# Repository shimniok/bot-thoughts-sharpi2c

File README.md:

A2D converts analog for you and presents it digitally through I2C, SPI or Serial. 
The onboard ATtiny performs oversampling and filtering to reduce noise. Flexible and hackable, 
you can program the device with AVRISP and make use of any of the exposed GPIO pins.

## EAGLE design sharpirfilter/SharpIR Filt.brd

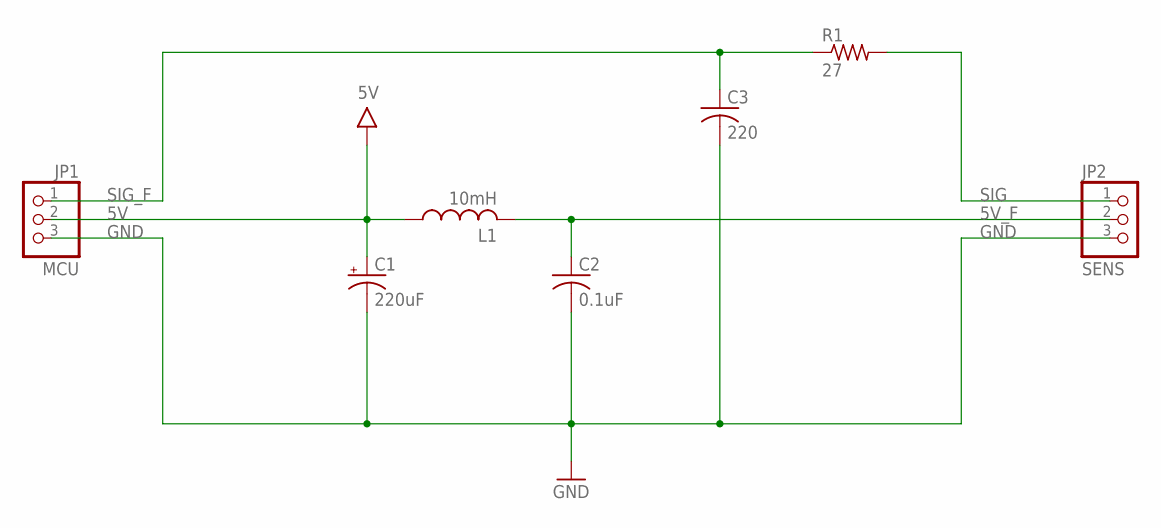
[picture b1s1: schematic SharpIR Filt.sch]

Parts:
C1: 220uF; PANASONIC_C
C2: 0.1uF; C0603
C3: 220; C0603
JP1: MCU; 1X03M
JP2: SENS; 1X03M
L1: 10mH; L5650M
R1: 27; R0603

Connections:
5V: C1.+, JP1.2, L1.1
5V_F: C2.1, JP2.2, L1.2
GND: C1.-, C2.2, C3.2, JP1.3, JP2.3
SIG: JP2.1, R1.2
SIG_F: C3.1, JP1.1, R1.1

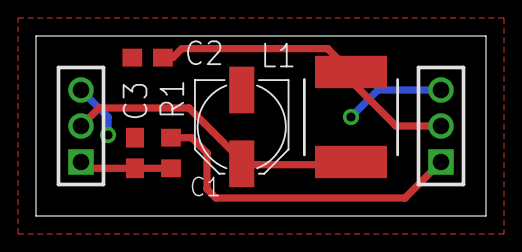
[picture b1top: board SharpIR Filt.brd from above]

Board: 2 copper layers, 25.0 x 10.0 mm, 7 parts (0 on the bottom side), 5 nets.

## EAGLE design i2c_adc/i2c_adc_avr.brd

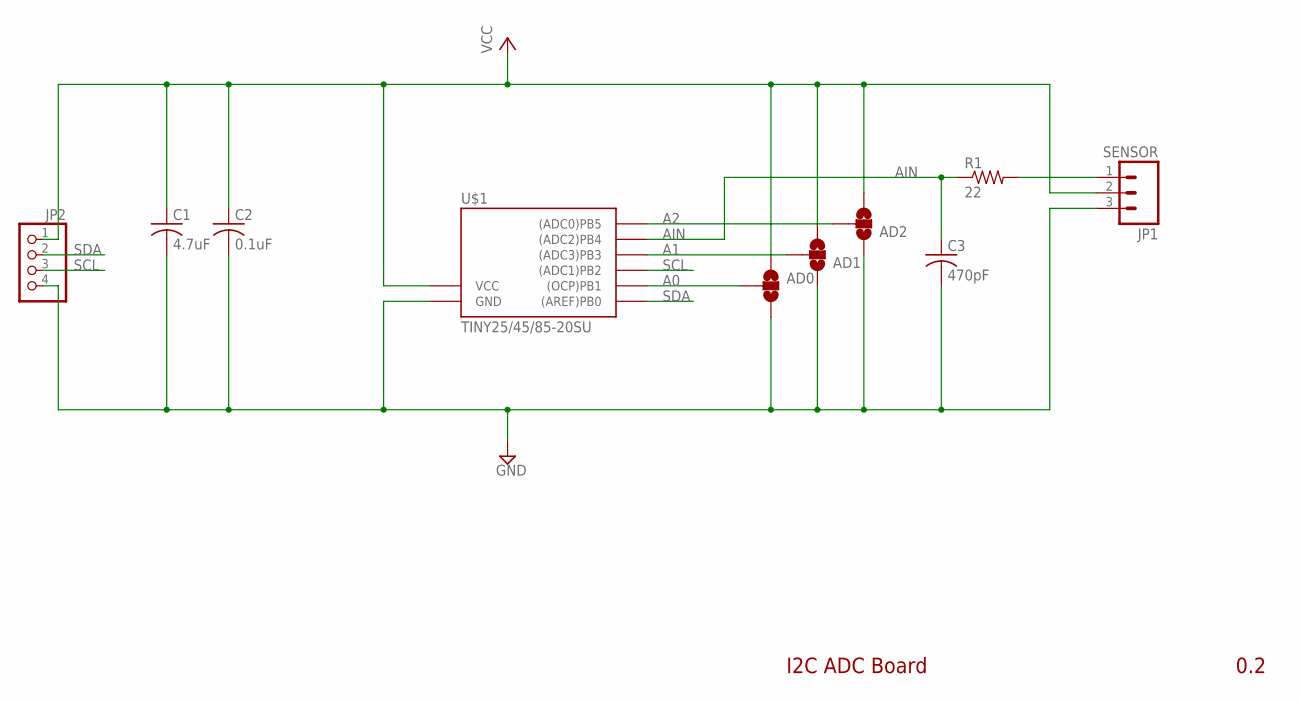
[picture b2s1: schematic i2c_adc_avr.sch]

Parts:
AD0, AD1, AD2: SOLDERJUMPER_2WAYS; SJ_3
C1: 4.7uF; C0603
C2: 0.1uF; C0603
C3: 470pF; C0603
JP1: SENSOR; 1X03
JP2: PINHD-1X04_2.54-S; 1X04-S
R1: 22; R0603
U$1: TINY25/45/85-20SU; SOIC8

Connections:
A0: AD0.2, U$1.6 ((OCP)PB1)
A1: AD1.2, U$1.2 ((ADC3)PB3)
A2: AD2.2, U$1.1 ((ADC0)PB5)
AIN: C3.1, R1.1, U$1.3 ((ADC2)PB4)
GND: AD0.3, AD1.1, AD2.1, C1.2, C2.2, C3.2, JP1.3, JP2.4, U$1.4 (GND)
unnamed: JP1.1, R1.2
SCL: JP2.3, U$1.7 ((ADC1)PB2)
SDA: JP2.2, U$1.5 ((AREF)PB0)
VCC: AD0.1, AD1.3, AD2.3, C1.1, C2.1, JP1.2, JP2.1, U$1.8 (VCC)

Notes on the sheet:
I2C ADC Board
0.2

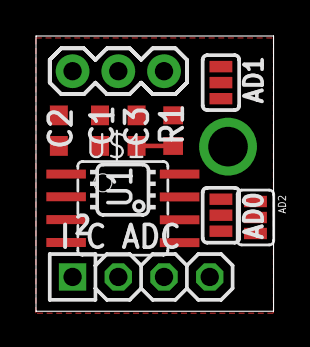
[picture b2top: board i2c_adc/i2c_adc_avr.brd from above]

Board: 2 copper layers, 13.2 x 15.3 mm, 10 parts (0 on the bottom side), 9 nets.

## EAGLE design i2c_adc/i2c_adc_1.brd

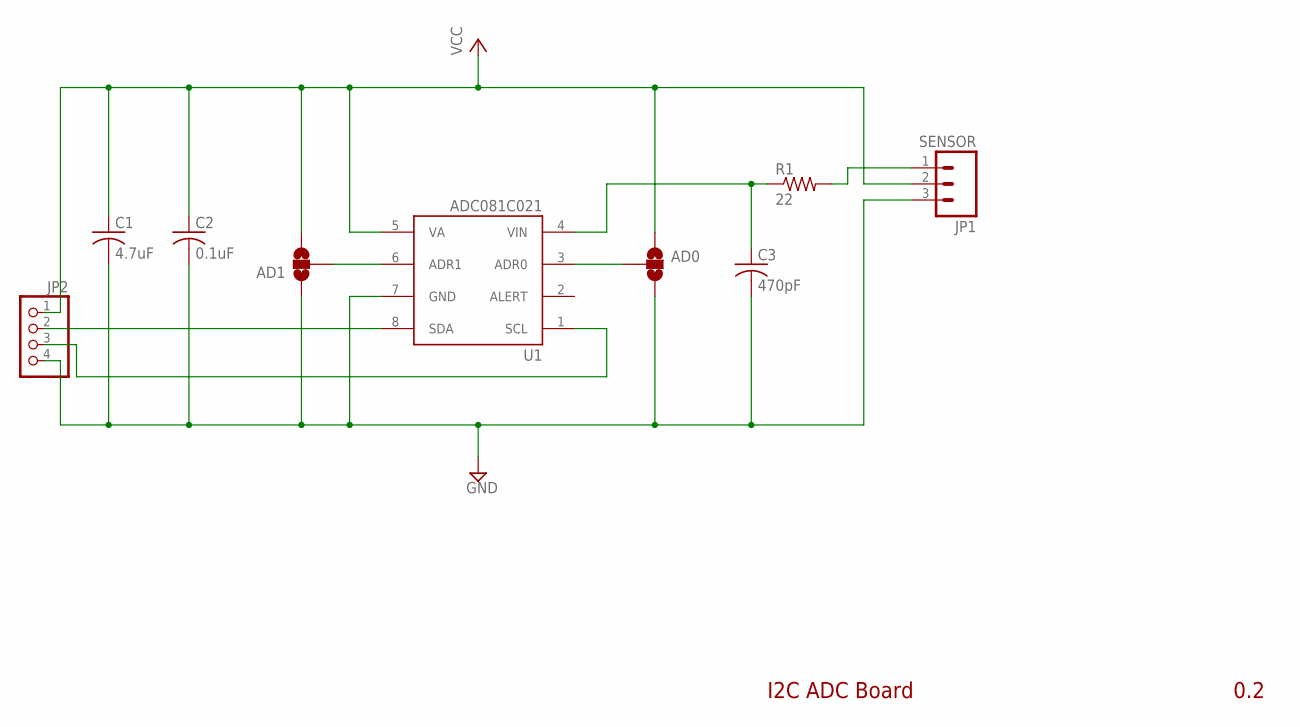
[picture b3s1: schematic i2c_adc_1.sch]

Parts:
AD0, AD1: SOLDERJUMPER_2WAYS; SJ_3
C1: 4.7uF; C0603
C2: 0.1uF; C0603
C3: 470pF; C0603
JP1: SENSOR; 1X03
JP2: PINHD-1X04_2.54-S; 1X04-S
R1: 22; R0603
U1: ADC081C021; MSOP8_0.65

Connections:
GND: AD0.3, AD1.1, C1.2, C2.2, C3.2, JP1.3, JP2.4, U1.7 (GND)
unnamed: JP1.1, R1.2
unnamed: AD1.2, U1.6 (ADR1)
unnamed: AD0.2, U1.3 (ADR0)
unnamed: C3.1, R1.1, U1.4 (VIN)
SCL: JP2.3, U1.1 (SCL)
SDA: JP2.2, U1.8 (SDA)
VCC: AD0.1, AD1.3, C1.1, C2.1, JP1.2, JP2.1, U1.5 (VA)

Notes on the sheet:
I2C ADC Board
0.2

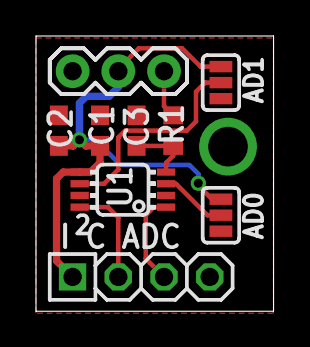
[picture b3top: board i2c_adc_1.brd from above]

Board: 2 copper layers, 13.2 x 15.3 mm, 9 parts (0 on the bottom side), 8 nets.

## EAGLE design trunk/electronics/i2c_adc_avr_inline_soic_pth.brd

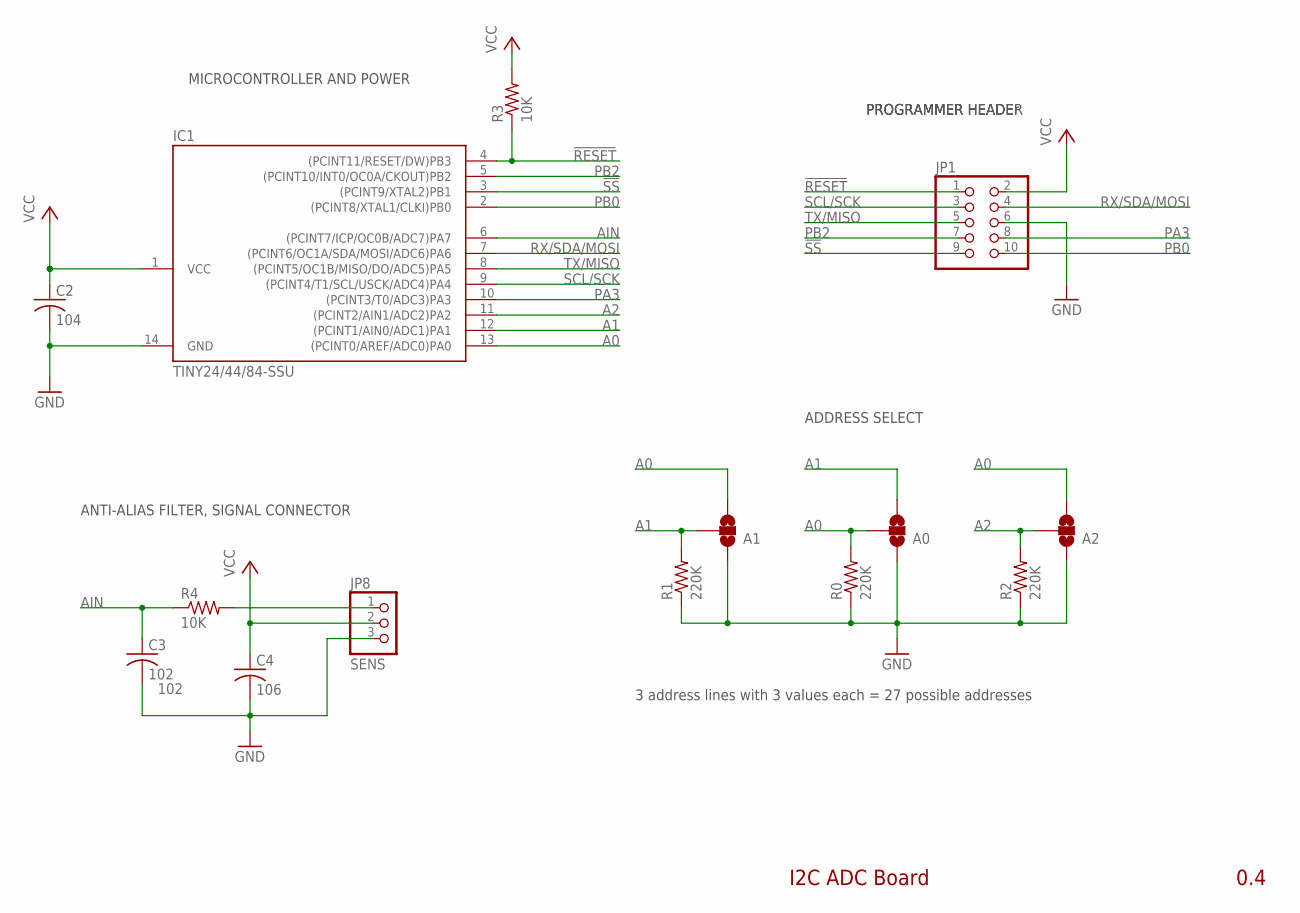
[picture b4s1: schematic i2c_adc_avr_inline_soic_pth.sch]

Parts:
A0, A1, A2: SJ_3
C2: 104; C0603; PARTNO C1608X7R1E104K080AA
C3: 102; C0603; PARTNO CL10B102KB8SFNC
C4: 106; C0603; PARTNO CL10A106MP8NNNC
IC1: TINY24/44/84-SSU; SOIC14
JP1: PINHD-2X05_2.54-90°; 2X05/90
JP8: SENS; 1X03-S
R0, R1, R2: 220K; R0603; PARTNO RC1608J224CS
R3, R4: 10K; R0603; PARTNO 1622829-1

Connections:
!RESET: IC1.4 ((PCINT11/RESET/DW)PB3), JP1.1, R3.1
!SS: IC1.3 ((PCINT9/XTAL2)PB1), JP1.9
A0: A0.2, A1.3, A2.3, IC1.13 ((PCINT0/AREF/ADC0)PA0), R0.2
A1: A0.3, A1.2, IC1.12 ((PCINT1/AIN0/ADC1)PA1), R1.2
A2: A2.2, IC1.11 ((PCINT2/AIN1/ADC2)PA2), R2.2
AIN: C3.1, IC1.6 ((PCINT7/ICP/OC0B/ADC7)PA7), R4.1
GND: A0.1, A1.1, A2.1, C2.2, C3.2, C4.2, IC1.14 (GND), JP1.6, JP8.3, R0.1, R1.1, R2.1
unnamed: JP8.1, R4.2
PA3: IC1.10 ((PCINT3/T0/ADC3)PA3), JP1.8
PB0: IC1.2 ((PCINT8/XTAL1/CLKI)PB0), JP1.10
PB2: IC1.5 ((PCINT10/INT0/OC0A/CKOUT)PB2), JP1.7
RX/SDA/MOSI: IC1.7 ((PCINT6/OC1A/SDA/MOSI/ADC6)PA6), JP1.4
SCL/SCK: IC1.9 ((PCINT4/T1/SCL/USCK/ADC4)PA4), JP1.3
TX/MISO: IC1.8 ((PCINT5/OC1B/MISO/DO/ADC5)PA5), JP1.5
VCC: C2.1, C4.1, IC1.1 (VCC), JP1.2, JP8.2, R3.2

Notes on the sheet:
I2C ADC Board
0.4
ADDRESS SELECT
MICROCONTROLLER AND POWER
ANTI-ALIAS FILTER, SIGNAL CONNECTOR
3 address lines with 3 values each = 27 possible addresses
PROGRAMMER HEADEr
PROGRAMMER HEADER

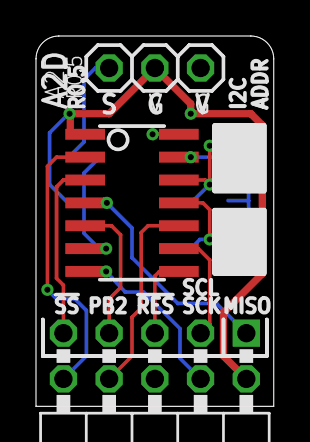
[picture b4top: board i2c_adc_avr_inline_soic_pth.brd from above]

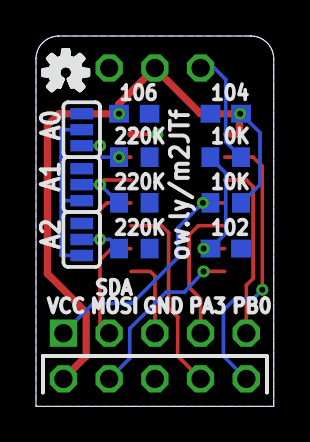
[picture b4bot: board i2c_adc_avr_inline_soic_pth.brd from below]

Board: 2 copper layers, 13.2 x 20.6 mm, 14 parts (11 on the bottom side), 15 nets.

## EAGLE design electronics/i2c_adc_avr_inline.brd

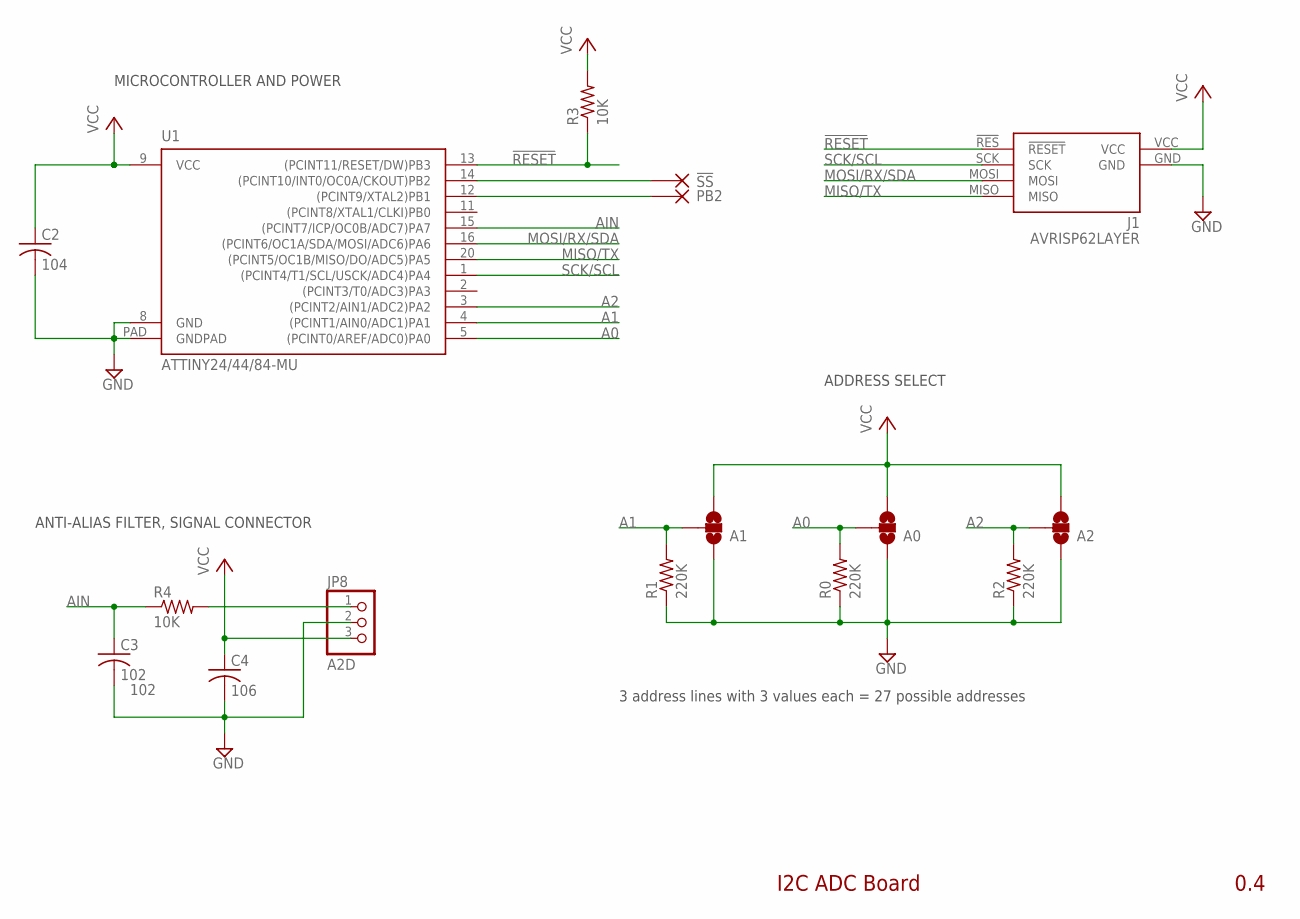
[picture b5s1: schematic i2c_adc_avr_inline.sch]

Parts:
A0, A1, A2: SJ_3
C2: 104; C0603; PARTNO C1608X7R1E104K080AA
C3: 102; C0603; PARTNO CL10B102KB8SFNC
C4: 106; C0603; PARTNO CL10A106MP8NNNC
J1: AVRISP62LAYER; 2X3_2LAYER
JP8: A2D; 1X03-S
R0, R1, R2: 220K; R0603; PARTNO RC1608J224CS
R3, R4: 10K; R0603; PARTNO 1622829-1
U1: ATTINY24/44/84-MU; 20MLF_0.5
X1: !SS; PAD0.07X0.15
X4: PB2; PAD0.07X0.15

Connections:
!RESET: J1.!RES (!RESET), R3.1, U1.13 ((PCINT11/RESET/DW)PB3)
A0: A0.2, R0.2, U1.5 ((PCINT0/AREF/ADC0)PA0)
A1: A1.2, R1.2, U1.4 ((PCINT1/AIN0/ADC1)PA1)
A2: A2.2, R2.2, U1.3 ((PCINT2/AIN1/ADC2)PA2)
AIN: C3.1, R4.1, U1.15 ((PCINT7/ICP/OC0B/ADC7)PA7)
GND: A0.1, A1.1, A2.1, C2.2, C3.2, C4.2, J1.GND, JP8.2, R0.1, R1.1, R2.1, U1.8 (GND), U1.PAD (GNDPAD)
MISO/TX: J1.MISO, U1.20 ((PCINT5/OC1B/MISO/DO/ADC5)PA5)
MOSI/RX/SDA: J1.MOSI, U1.16 ((PCINT6/OC1A/SDA/MOSI/ADC6)PA6)
unnamed: JP8.1, R4.2
unnamed: U1.14 ((PCINT10/INT0/OC0A/CKOUT)PB2), X1.P$1
unnamed: U1.12 ((PCINT9/XTAL2)PB1), X4.P$1
SCK/SCL: J1.SCK, U1.1 ((PCINT4/T1/SCL/USCK/ADC4)PA4)
VCC: A0.3, A1.3, A2.3, C2.1, C4.1, J1.VCC, JP8.3, R3.2, U1.9 (VCC)

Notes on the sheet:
I2C ADC Board
0.4
ADDRESS SELECT
MICROCONTROLLER AND POWER
ANTI-ALIAS FILTER, SIGNAL CONNECTOR
3 address lines with 3 values each = 27 possible addresses

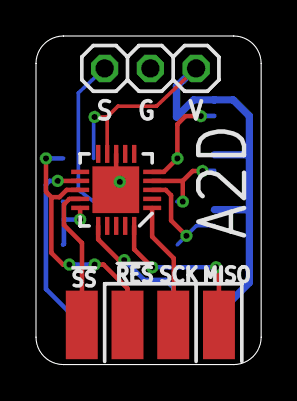
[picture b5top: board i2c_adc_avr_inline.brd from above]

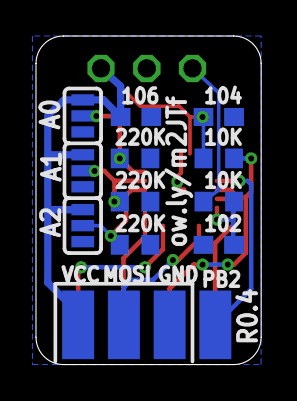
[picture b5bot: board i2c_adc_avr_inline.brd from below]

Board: 2 copper layers, 12.5 x 18.3 mm, 16 parts (12 on the bottom side), 13 nets.

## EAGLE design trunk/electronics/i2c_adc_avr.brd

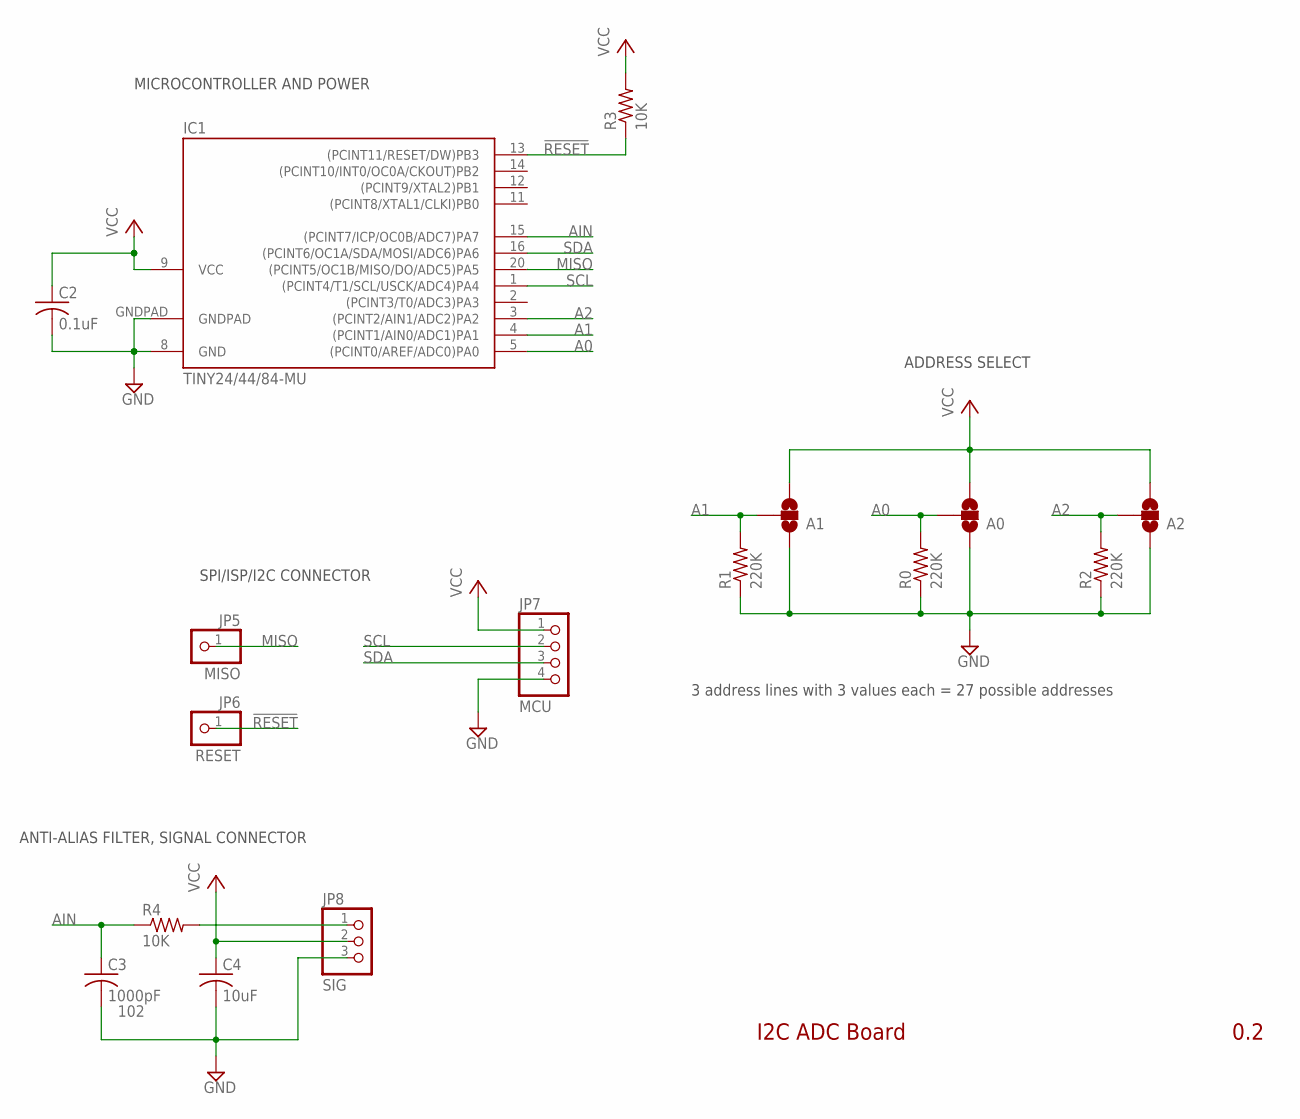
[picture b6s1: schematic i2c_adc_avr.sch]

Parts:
A0, A1, A2: SJ_3
C2: 0.1uF; C0603; PARTNO C1608X7R1E104K080AA
C3: 1000pF; C0603; PARTNO CL10B102KB8SFNC
C4: 10uF; C0603; PARTNO CL10A106MP8NNNC
IC1: TINY24/44/84-MU; QFN/MLF20; PARTNO ATTINY44A-MU
JP5: MISO; 1X01
JP6: RESET; 1X01
JP7: MCU; 1X04-S
JP8: SIG; 1X03M
R0, R1, R2: 220K; R0603; PARTNO RC1608J224CS
R3, R4: 10K; R0603; PARTNO 1622829-1

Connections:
!RESET: IC1.13 ((PCINT11/RESET/DW)PB3), JP6.1, R3.1
A0: A0.2, IC1.5 ((PCINT0/AREF/ADC0)PA0), R0.2
A1: A1.2, IC1.4 ((PCINT1/AIN0/ADC1)PA1), R1.2
A2: A2.2, IC1.3 ((PCINT2/AIN1/ADC2)PA2), R2.2
AIN: C3.1, IC1.15 ((PCINT7/ICP/OC0B/ADC7)PA7), R4.1
GND: A0.1, A1.1, A2.1, C2.2, C3.2, C4.2, IC1.8 (GND), IC1.GNDPAD, JP7.4, JP8.3, R0.1, R1.1, R2.1
MISO: IC1.20 ((PCINT5/OC1B/MISO/DO/ADC5)PA5), JP5.1
unnamed: JP8.1, R4.2
SCL: IC1.1 ((PCINT4/T1/SCL/USCK/ADC4)PA4), JP7.2
SDA: IC1.16 ((PCINT6/OC1A/SDA/MOSI/ADC6)PA6), JP7.3
VCC: A0.3, A1.3, A2.3, C2.1, C4.1, IC1.9 (VCC), JP7.1, JP8.2, R3.2

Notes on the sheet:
I2C ADC Board
0.2
ADDRESS SELECT
MICROCONTROLLER AND POWER
ANTI-ALIAS FILTER, SIGNAL CONNECTOR
SPI/ISP/I2C CONNECTOR
3 address lines with 3 values each = 27 possible addresses

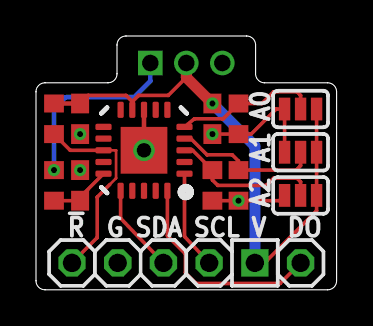
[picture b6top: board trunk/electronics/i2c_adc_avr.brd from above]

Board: 2 copper layers, 16.7 x 14.1 mm, 16 parts (1 on the bottom side), 11 nets.

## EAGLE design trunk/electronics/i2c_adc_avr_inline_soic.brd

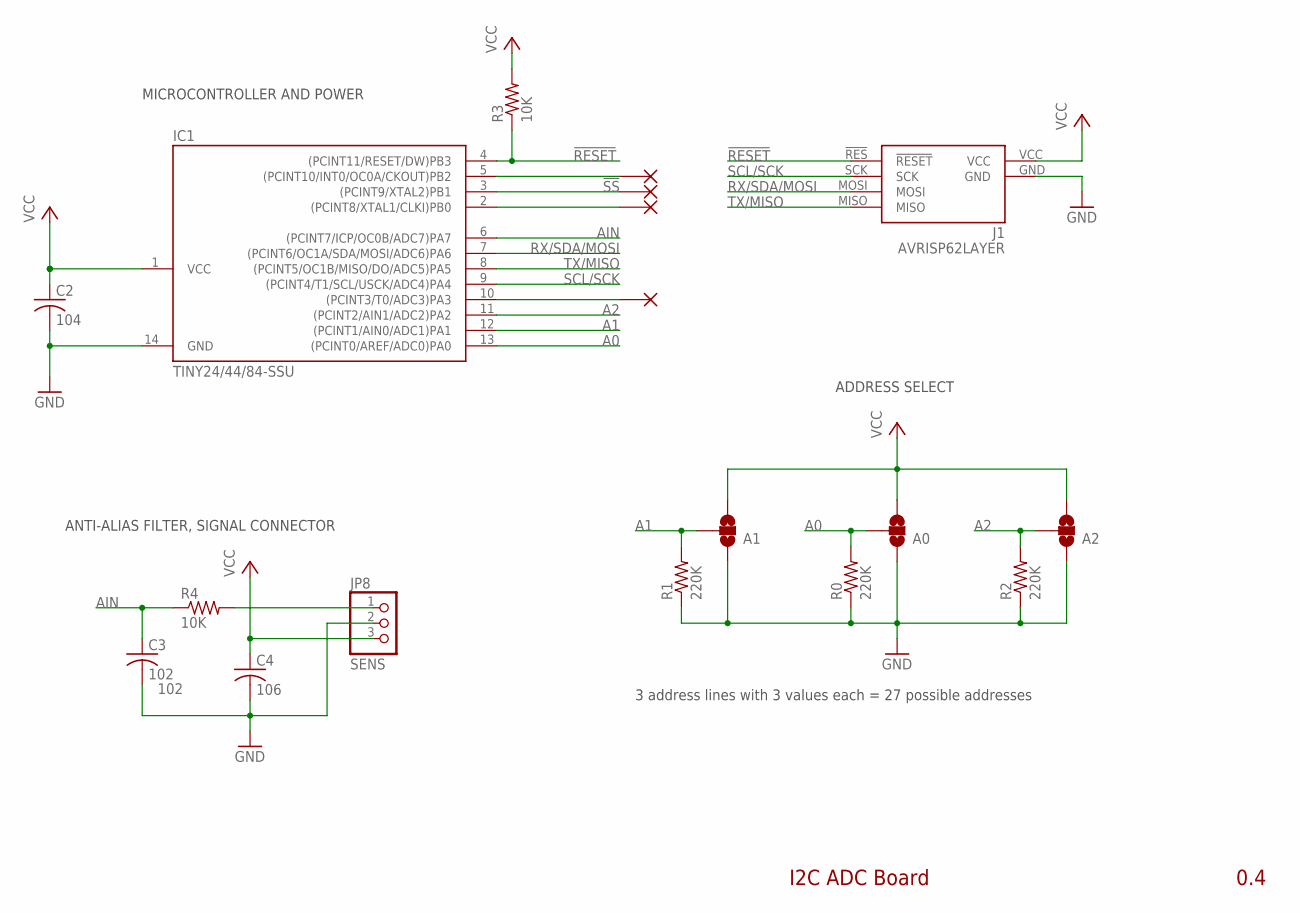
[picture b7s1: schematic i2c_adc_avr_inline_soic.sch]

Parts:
A0, A1, A2: SJ_3
C2: 104; C0603; PARTNO C1608X7R1E104K080AA
C3: 102; C0603; PARTNO CL10B102KB8SFNC
C4: 106; C0603; PARTNO CL10A106MP8NNNC
IC1: TINY24/44/84-SSU; SOIC14
J1: AVRISP62LAYER; 2X3_2LAYER
JP8: SENS; 1X03-S
R0, R1, R2: 220K; R0603; PARTNO RC1608J224CS
R3, R4: 10K; R0603; PARTNO 1622829-1
X1: PB2; PAD0.07X0.15
X2: !SS; PAD0.07X0.15
X3: PB0; PAD0.07X0.15
X4: PA3; PAD0.07X0.15

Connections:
!RESET: IC1.4 ((PCINT11/RESET/DW)PB3), J1.!RES (!RESET), R3.1
!SS: IC1.3 ((PCINT9/XTAL2)PB1), X2.P$1
A0: A0.2, IC1.13 ((PCINT0/AREF/ADC0)PA0), R0.2
A1: A1.2, IC1.12 ((PCINT1/AIN0/ADC1)PA1), R1.2
A2: A2.2, IC1.11 ((PCINT2/AIN1/ADC2)PA2), R2.2
AIN: C3.1, IC1.6 ((PCINT7/ICP/OC0B/ADC7)PA7), R4.1
GND: A0.1, A1.1, A2.1, C2.2, C3.2, C4.2, IC1.14 (GND), J1.GND, JP8.2, R0.1, R1.1, R2.1
unnamed: JP8.1, R4.2
unnamed: IC1.10 ((PCINT3/T0/ADC3)PA3), X4.P$1
unnamed: IC1.2 ((PCINT8/XTAL1/CLKI)PB0), X3.P$1
unnamed: IC1.5 ((PCINT10/INT0/OC0A/CKOUT)PB2), X1.P$1
RX/SDA/MOSI: IC1.7 ((PCINT6/OC1A/SDA/MOSI/ADC6)PA6), J1.MOSI
SCL/SCK: IC1.9 ((PCINT4/T1/SCL/USCK/ADC4)PA4), J1.SCK
TX/MISO: IC1.8 ((PCINT5/OC1B/MISO/DO/ADC5)PA5), J1.MISO
VCC: A0.3, A1.3, A2.3, C2.1, C4.1, IC1.1 (VCC), J1.VCC, JP8.3, R3.2

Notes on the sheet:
I2C ADC Board
0.4
ADDRESS SELECT
MICROCONTROLLER AND POWER
ANTI-ALIAS FILTER, SIGNAL CONNECTOR
3 address lines with 3 values each = 27 possible addresses

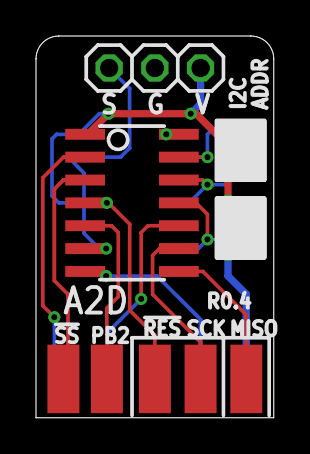
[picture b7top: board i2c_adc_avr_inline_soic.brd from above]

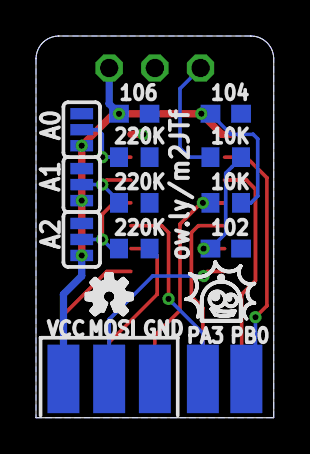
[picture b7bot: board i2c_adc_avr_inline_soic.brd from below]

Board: 2 copper layers, 13.2 x 21.2 mm, 18 parts (13 on the bottom side), 15 nets.

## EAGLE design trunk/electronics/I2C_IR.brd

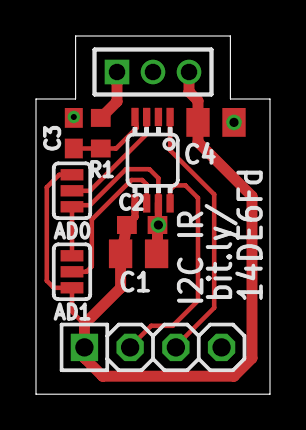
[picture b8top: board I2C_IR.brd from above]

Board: 2 copper layers, 13.0 x 19.9 mm, 10 parts (0 on the bottom side), 8 nets.

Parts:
C1: 4.7uF; C0805K
C2: 0.1uF; C0603
C3: 470pF; C0603
C4: 10uF; C0805K
JP1: MCU; 1X04-S
JP3: Sharp Module; 1X03M
R1: 22; R0603
SJ1: AD0; SJ_3
SJ2: AD1; SJ_3
U1: ADC081C021; MSOP8_0.65

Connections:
ADR0: SJ1.2, U1.3
ADR1: SJ2.2, U1.6
GND: C1.2, C2.2, C3.2, C4.2, JP1.4, JP3.2, SJ1.3, SJ2.3, U1.7
unnamed: C3.1, R1.1, U1.4
SCL: JP1.3, U1.1
SDA: JP1.2, U1.8
SIG: JP3.1, R1.2
VCC: C1.1, C2.1, C4.1, JP1.1, JP3.3, SJ1.1, SJ2.1, U1.5

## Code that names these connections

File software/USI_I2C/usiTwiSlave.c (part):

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#  define DDR_USI             DDRB
#  define PORT_USI            PORTB
#  define PIN_USI             PINB
#  define PORT_USI_SDA        PB5
#  define PORT_USI_SCL        PB7
#  define PIN_USI_SDA         PINB5
#  define PIN_USI_SCL         PINB7
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#  define DDR_USI             DDRA
#  define PORT_USI            PORTA
#  define PIN_USI             PINA
#  define PORT_USI_SDA        PA6
#  define PORT_USI_SCL        PA4
#  define PIN_USI_SDA         PINA6
#  define PIN_USI_SCL         PINA4
#  define USI_START_COND_INT  USISIF
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#  define DDR_USI             DDRB
#  define PORT_USI            PORTB
#  define PIN_USI             PINB
#  define PORT_USI_SDA        PB0
#  define PORT_USI_SCL        PB2
#  define PIN_USI_SDA         PINB0
#  define PIN_USI_SCL         PINB2
#  define USI_START_COND_INT  USISIF
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#  define DDR_USI             DDRB
#  define PORT_USI            PORTB
#  define PIN_USI             PINB
#  define PORT_USI_SDA        PB0
#  define PORT_USI_SCL        PB2
#  define PIN_USI_SDA         PINB0
#  define PIN_USI_SCL         PINB2
#  define USI_START_COND_INT  USISIF
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#  define DDR_USI             DDRB
#  define PORT_USI            PORTB
#  define PIN_USI             PINB
#  define PORT_USI_SDA        PB0
#  define PORT_USI_SCL        PB2
#  define PIN_USI_SDA         PINB0
#  define PIN_USI_SCL         PINB2
#  define USI_START_COND_INT  USISIF
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
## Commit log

2013-02-01 Initial directory structure.
2013-02-01 Initial revision
2013-02-01 Revised board layout
2013-02-01 Created wiki page through web user interface.
2013-02-01 Revised board layout per datasheet, single ground plane with join at chip ground location, no bottom traces, use tantalum bypass caps, etc.
2013-02-01 Edited wiki page Documentation through web user interface.
2013-02-01 Minor layout tweaks
2013-02-04 Revised board layout removing 'cut' per white paper I read.
2013-06-14 Added a folder to the repository
2013-06-14 Early revision of AVR based I2C adapter
2013-06-14 Initial revisions for serial and I2C solutions.
2013-06-14 Trying to fix warning icon
2013-06-14 Edited wiki page Home through web user interface.
2013-06-14 Edited wiki page Installaton through web user interface.
2013-06-14 Deleted wiki page Installaton through web user interface.
2013-06-14 Edited wiki page Installation through web user interface.
2013-06-14 Edited wiki page Protocol through web user interface.
2013-06-14 Edited wiki page Examples through web user interface.
2013-06-18 Edited wiki page FirmwareUpdate through web user interface.
2013-06-19 Rev 0.3 as built (version is mislabeled on silk)
2013-06-19 Separated adc, filter into modules. Added address module for determining address from solder jumpers, started code for distance conversion, revised how registers / parameters are updated through I2C.
2013-08-07 A2D soic as ordered, migrated to soic, added silk spots for writing address, moved lots around, changed end connector exposed more pins
2013-08-07 Changed footprint, layout
2013-08-07 Minor changes to i2cadc project
2013-08-07 Updated version of the inline with QFN, moved layout, added !SS and PB2 pins, using 2-side pads for connectors
2013-08-21 Modified layouts, routing.
2013-08-21 PTH connector version with some additional fixes
2013-08-21 Initial version of backplane idea
2013-08-21 latest .cproject
2013-08-21 oops
2013-08-21 Initial revision of USI I2C library
2013-08-21 Initial revision of USI Serial library
2013-08-21 Removed numerous routines/modules into separate libraries.
2013-08-21 Updated documentation
2013-08-21 Removed Debug configuration
2013-08-21 Adding early versions of A2Dserial and A2Dspi firmware
2013-08-21 Renamed i2cadc to A2Di2c
2013-08-21 Iniital version of examples
2013-08-21 Added makefiles, tweaked adc code to use registers
2013-08-21 Renamed makefile to Makefile
2013-08-22 Optimized for code size removing pow().
2013-08-22 Optimized for code size, modified makefile.
2013-08-22 Removed Eclipse files from source control
2013-08-22 Optimized code for size per AVR035 and removed Eclipse files from source control
2013-08-22 Optimized code for size, removed Eclipse files from source control, revised Makefile
2013-08-22 Removed math.h include, unnecessary.
2013-08-22 Initial readme instructions for use with various IDEs.
2013-12-04 Edited wiki page Registers through web user interface.
2015-05-04 Migrating wiki contents from Google Code
2015-05-10 Added I2C ADC board
2015-05-10 Added I2C ADC sketchup and zip
2015-05-10 Added sharp IR filter electronics
2015-05-10 Added notes file
2015-05-10 Added some text file notes
2015-05-10 Added notes files
2015-05-10 added gitignore

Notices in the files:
software/USI_I2C/usiTwiSlave.c:
This program is free software; you can redistribute it and/or modify it under the
terms of the GNU General Public License as published by the Free Software
parts and their libraries:
SparkFun: Licensing: CC v3.0 Share-Alike You are welcome to use this library for commercial purposes.
